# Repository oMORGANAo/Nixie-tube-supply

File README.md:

# Nixie-tube-supply

This Nixie tube supply board was built as part of my Power Electronics course at KU Leuven - Campus GroupT in 2022-2023.

Design specifications for this board are 9V Input, and 170V Output (10 mA max). The MAX1771CPA+ step-up switching controller from MAXIM INTEGRATED was used for this application. All design choices and measurements can be found in the PDF document in the main branch.

PCB front side:

All the design files are under GPL3 and can be freely used for personal projects where this device can be of use.

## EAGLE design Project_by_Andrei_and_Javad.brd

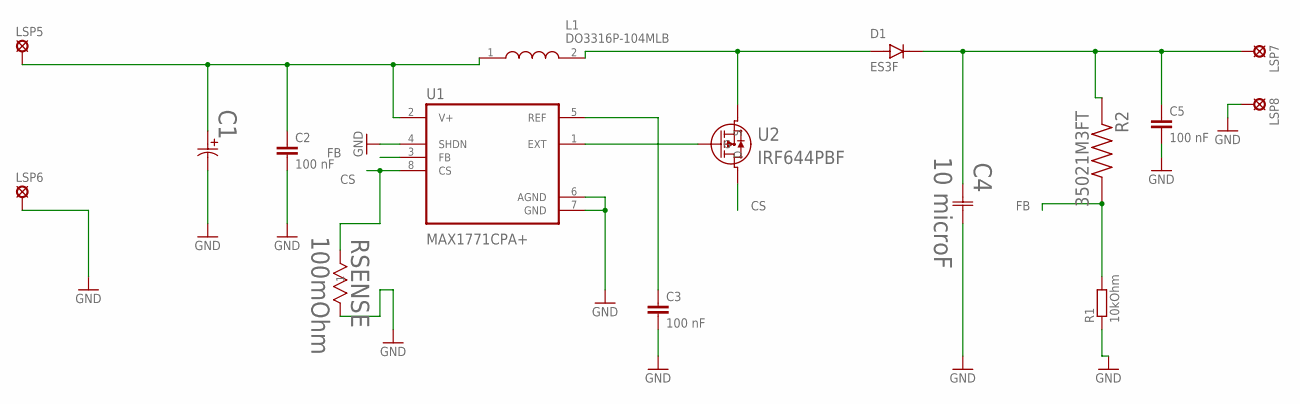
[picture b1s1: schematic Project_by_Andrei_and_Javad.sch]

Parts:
C1: 100 microF; CAPMP7.6X4.3_4.3N_KEM
C2, C3: 100 nF; C0805
C4: 10 microF; CAP_EB_G17_PAN
C5: 100 nF; C1206
D1: ES3F; DIOM6859X262N
L1: DO3316P-104MLB; DO3316P102MLB
LSP5, LSP6, LSP7, LSP8: LSP13
R1: 10kOhm; R0805
R2: 35021M3FT; RESC5025X120N
RSENSE: 100mOhm; YAG_R2512_YAG
U1: MAX1771CPA+; DIP794W47P254L991H457Q8
U2: IRF644PBF; TO220AB_VIS

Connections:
CS: RSENSE.1, U1.8 (CS), U2.2 (D)
FB: R1.2, R2.2, U1.3 (FB)
GND: C1.2, C2.2, C3.2, C4.2, C5.2, LSP6.MP, LSP8.MP, R1.1, RSENSE.2, U1.4 (SHDN), U1.6 (AGND), U1.7 (GND)
unnamed: C1.1, C2.1, L1.1, LSP5.MP, U1.2 (V+)
unnamed: U1.1 (EXT), U2.1 (G)
unnamed: D1.A, L1.2, U2.3 (S)
unnamed: C3.1, U1.5 (REF)
unnamed: C4.1, C5.1, D1.C (K), LSP7.MP, R2.1

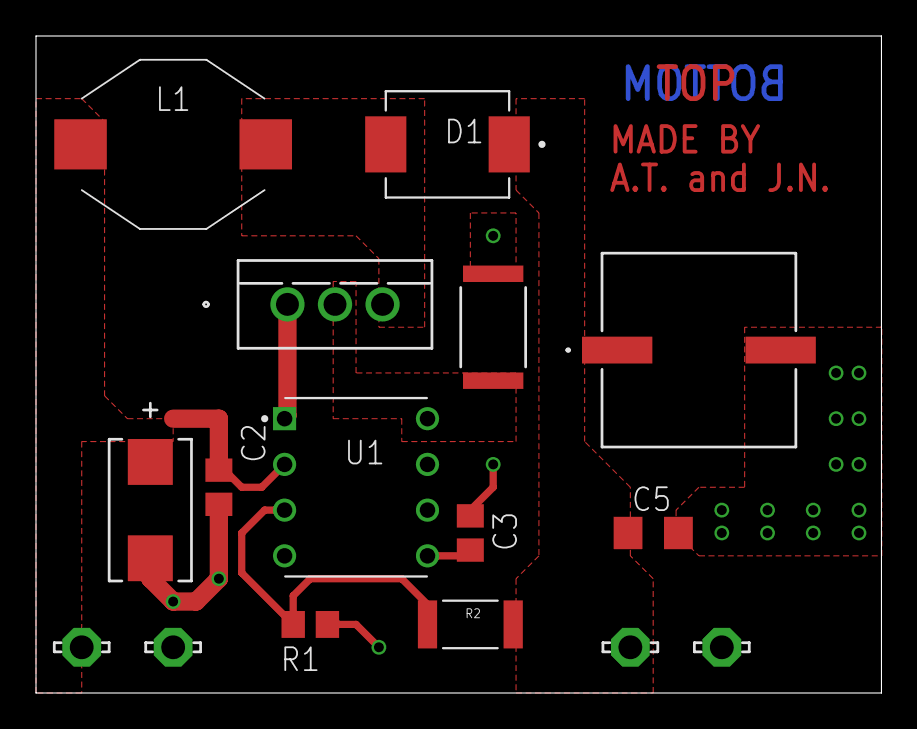
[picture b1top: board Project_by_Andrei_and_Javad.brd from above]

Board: 2 copper layers, 47.0 x 36.5 mm, 16 parts (0 on the bottom side), 8 nets.

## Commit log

2024-01-30 Create LICENSE

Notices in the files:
parts and their libraries:
COPYRIGHT: Copyright (C) 2022 Ultra Librarian. All rights reserved.
